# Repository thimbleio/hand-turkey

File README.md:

## Thimble Hand Turkey Project
As a fun holiday-themed activity, we took a break in the office to draw grade-school-style hand-turkeys. This project is the result. Feel free to duplicate our work and have some fun making your own!

### Instructions

NOTE: There are slightly more detailed instructions on our [blog](https://blog.thimble.io/happy-thanksgiving-from-thimble-98a42b42d3b0). If you get stuck, ask on our [forums](https://learning.thimble.io/forum/t/happy-thanksgiving/) or send us an email.

Start by printing out the [template PDF file](drawPage.pdf). Then, trace your hand.

Clone or download this repository to your computer.

Scan your drawing into your computer and use [KiCAD](http://kicad-pcb.org/)'s Bitmap2Component tool to import your design to the silkscreen layer. We recommend scaling your design to fit within a 10x10cm square to be able to utilize low-cost rapid PCB prototyping services.

Trace around your hand in KiCAD on the edge cuts layer and move components around to fit your design.

Generate your gerbers and drill files and either make your own printed circuit board or have it manufactured.

Enjoy! Please share your creation with us on social media using our hashtag, #madewiththimble for a chance to win a prize.

For more fun electronics projects visit [our website](https://www.thimble.io/) and make sure to check out our [blog](https://blog.thimble.io/) and [learning platform](https://learning.thimble.io/).

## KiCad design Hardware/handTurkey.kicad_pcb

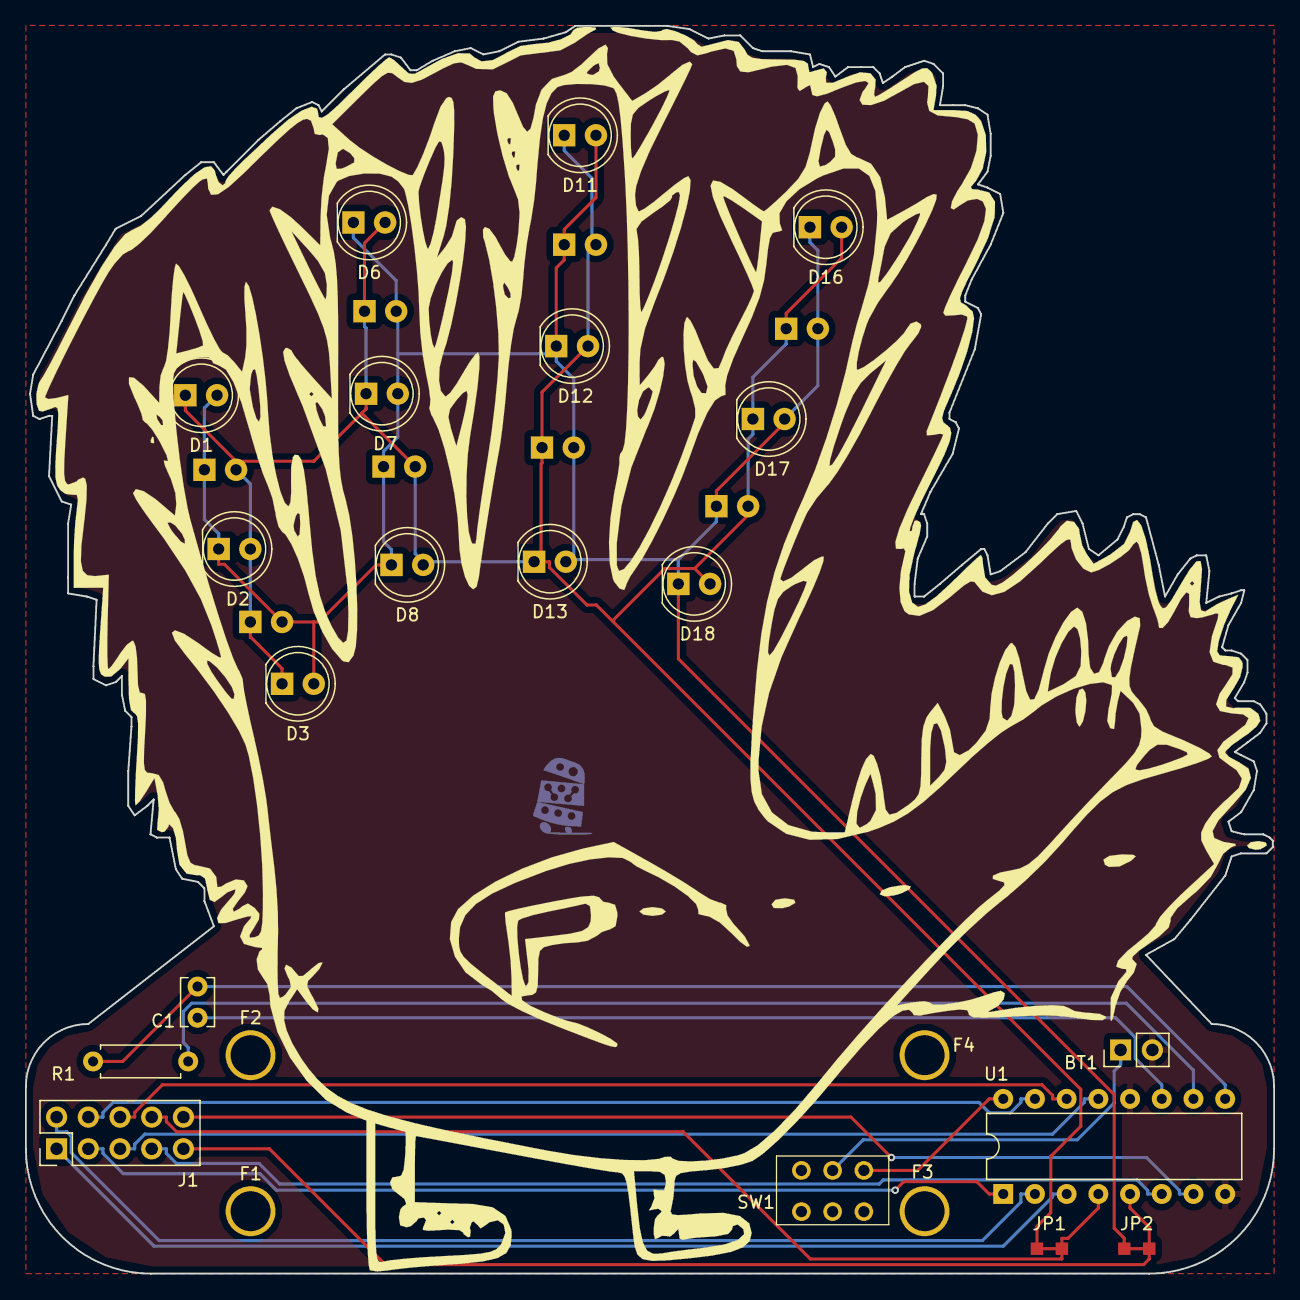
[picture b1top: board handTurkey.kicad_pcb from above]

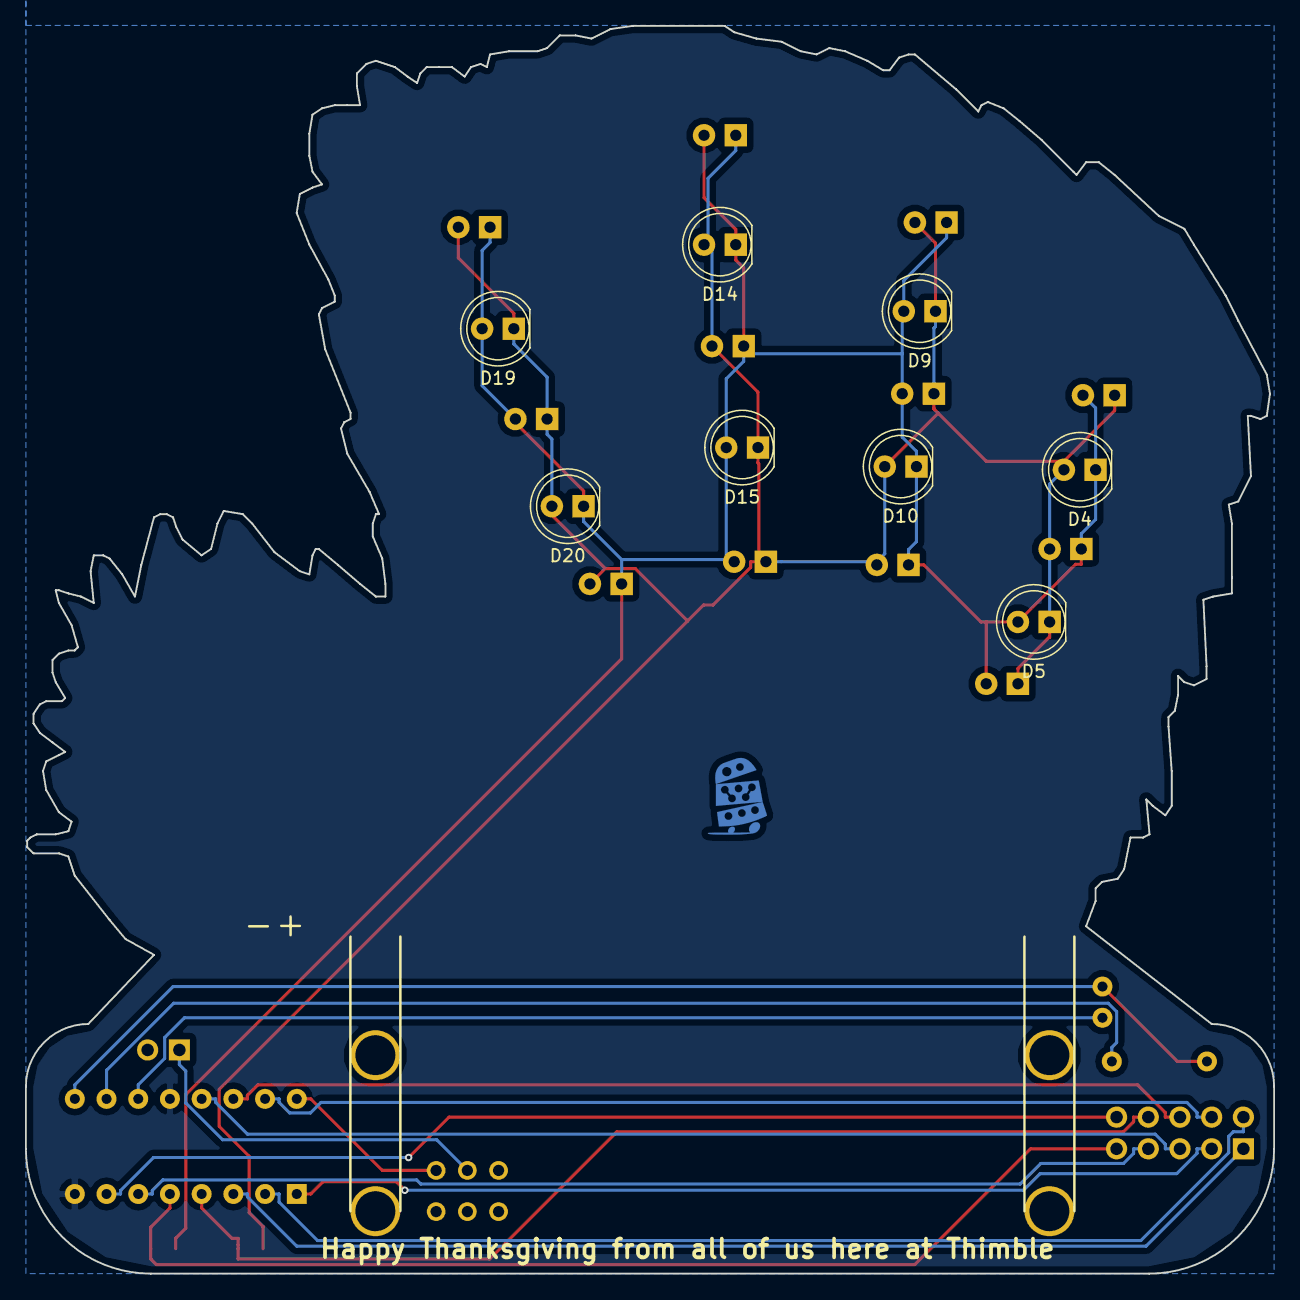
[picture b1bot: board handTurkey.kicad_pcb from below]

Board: 2 copper layers, 100.0 x 100.0 mm, 33 parts (9 on the bottom side), 18 nets.

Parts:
BT1: Battery; Pin_Header_Straight_1x02_Pitch2.54mm
C1: 0.22uF; C_Disc_D3.8mm_W2.6mm_P2.50mm
D1, D2, D3, D4, D5, D6, D7, D8, D9, D10, D11, D12, D13, D14, D15, D16, D17, D18, D19, D20: LED; LED_D5.0mm
F1, F2, F3, F4: 3mHole; M3Hole
J1: CONN_01X10; Pin_Header_Straight_2x05_Pitch2.54mm
JP1: Q4 Jump; jumper
JP2: Q5 Jump; jumper
R1: 100K; R_Axial_DIN0207_L6.3mm_D2.5mm_P7.62mm_Horizontal
SW1: SW_DPDT_x2; slideJS
U1: 4060; DIP-16_W7.62mm
thimG***: LOGO; Thimble_Logo_copper

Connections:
/Q4: J1.10, U1.7
/Q5: J1.9, JP2.2, U1.5
/Q6: J1.8, JP1.1, U1.4
/Q7: J1.7, U1.6
/Q8: J1.6, U1.14
/Q9: J1.5, U1.13
/Q10: J1.4, U1.15
/Q12: J1.3, U1.1
/Q13: J1.2, U1.2
/Q14: J1.1, U1.3
GND: BT1.2, U1.8, U1.12
unnamed: BT1.1, SW1.2
unnamed: C1.1, U1.11
unnamed: C1.2, R1.1, U1.9
unnamed: D1.1, D2.2, D3.1, D4.2, D5.1, D6.2, D7.1, D8.2, D9.1, D10.2, D11.1, D12.2, D13.1, D14.2, D15.1, D16.2, D17.1, D18.2, D19.1, D20.2, JP1.2
unnamed: D1.2, D2.1, D3.2, D4.1, D5.2, D6.1, D7.2, D8.1, D9.2, D10.1, D11.2, D12.1, D13.2, D14.1, D15.2, D16.1, D17.2, D18.1, D19.2, D20.1, JP2.1
unnamed: R1.2, U1.10
VDD: SW1.1, U1.16

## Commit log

2017-11-22 Initial commit of hand turkey project
2017-11-22 Add README and LICENSE
2017-11-22 Add a couple of links and the youtube video to the readme
